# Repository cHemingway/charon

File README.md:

Remake of [carrotIndustries Pluto](https://github.com/carrotIndustries/pluto) watch (see OLD_README.md) to use Cypress PSoC4208 BLE microcontroller

Not yet manufactured, use at your own risk

PSoC4 used as it is only BLE MCU I could find with Segment LCD support.

# Credits
Major thanks to Carrot Industries for reverse engineering the display and mechanicals, this project would not be possible without this.

BME680 3D model from [3D Content Central](http://www.3dcontentcentral.com/download-model.aspx?catalogid=171&id=806790)

# Changes
- MSP430 replaced with Cypress PsOC4208 BLE MCU
- Magentometer is replaced with Bosch [BME680](https://www.bosch-sensortec.com/bst/products/all_products/bme680) Temp/Pressure/Humidity/Gas sensor
- IR reciever removed
- LED polarity fixed to save GPIO

# TODO
- Manufacture
- Bring up
- Port existing Pluto firmware

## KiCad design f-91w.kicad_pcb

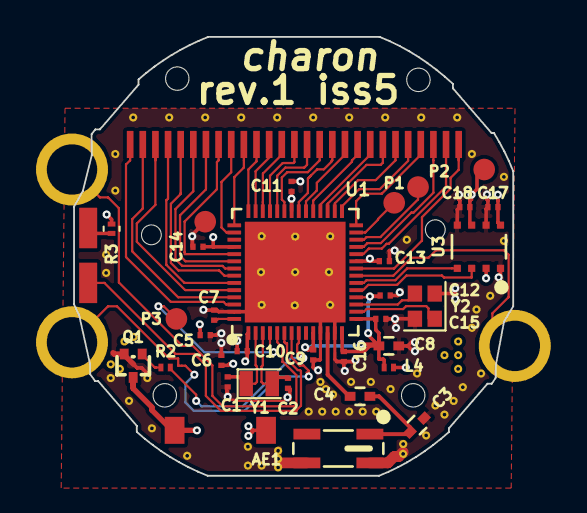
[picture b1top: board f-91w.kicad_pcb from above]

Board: 4 copper layers, 24.4 x 24.4 mm, 40 parts (0 on the bottom side), 50 nets.

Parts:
AE1: 2450AT42E0100
C1: 24pF; C_0201_NoSilk
C2: 47pF; C_0201_NoSilk
C3, C4: C_Small; C_0402
C5, C6, C7: 1uF; C_0201_NoSilk
C8: 10uF; C_0402
C9, C10, C11, C12, C13, C14, C15, C16, C17, C18: 100nF; C_0201_NoSilk
L4: 330R@100MHz; R_0201_NoSilk
P1, P2, P3: CONN_01X01; TP_1.2mm
P5, P6, P7, P8, P9, P10, P11, P13, P14: CONN_01X01; 1pin
Q1: BC847BTT1; SOT416
R2: 47k; R_0201_NoSilk
R3: 100; R_0201
U1: CY8C4248LQI-BL483; Cypress_QFN56
U2: LCD-F-91W
U3: BME680
Y1: 32.768KHz; Crystal_SMD_Abracon_ABS06-2pin_2.0x1.2mm
Y2: 24MHz; Crystal_SMD_2016-4pin_2.0x1.6mm

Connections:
//XRES: P3.1, U1.4
/BUZ: P9.1, Q1.3
/BUZ_EN: R2.1, U1.8
/B_ALARM: P7.1, U1.21
/B_LIGHT: P5.1, U1.5
/B_MODE: P6.1, U1.7
/LCD_COM1: U1.48, U2.7
/LCD_COM2: U1.47, U2.8
/LCD_COM3: U1.44, U2.9
/LCD_SEG1: U1.54, U2.1
/LCD_SEG2: U1.53, U2.2
/LCD_SEG3: U1.52, U2.3
/LCD_SEG4: U1.51, U2.4
/LCD_SEG5: U1.50, U2.5
/LCD_SEG6: U1.49, U2.6
/LCD_SEG7: U1.43, U2.10
/LCD_SEG8: U1.42, U2.11
/LCD_SEG9: U1.41, U2.12
/LCD_SEG10: U1.40, U2.13
/LCD_SEG11: U1.39, U2.14
/LCD_SEG12: U1.38, U2.15
/LCD_SEG13: U1.37, U2.16
/LCD_SEG14: U1.35, U2.17
/LCD_SEG15: U1.34, U2.18
/LCD_SEG16: U1.33, U2.19
/LCD_SEG17: U1.32, U2.20
/LCD_SEG18: U1.31, U2.21
/LCD_SEG19: U1.30, U2.22
/LCD_SEG20: U1.29, U2.23
/LCD_SEG21: U1.28, U2.24
/LCD_SEG22: U1.25, U2.25
/LCD_SEG23: U1.24, U2.26
/LCD_SEG24: U1.22, U2.27
/LED_1: P11.1, U1.6
/SCL: U1.20, U3.4
/SDA: U1.19, U3.3
/SWCLK: P1.1, U1.27
/SWDIO: P2.1, U1.26
GND: AE1.2, C1.2, C2.2, C3.2, C5.1, C6.2, C7.2, C8.2, C9.2, C10.2, C11.2, C12.2, C13.2, C14.2, C15.2, C16.2, C17.2, C18.2, P13.1, Q1.2, U1.11, U1.13, U1.55, U1.57, U3.1, U3.5, U3.7, Y2.2, Y2.4
unnamed: AE1.1, C3.1, C4.2
unnamed: C1.1, U1.2, Y1.1
unnamed: C2.1, U1.3, Y1.2
unnamed: C4.1, U1.12
unnamed: C5.2, U1.56
unnamed: P10.1, R3.1
unnamed: Q1.1, R2.2
unnamed: U1.16, Y2.1
unnamed: U1.17, Y2.3
VCC: C6.1, C7.1, C10.1, C11.1, C13.1, C14.1, C17.1, C18.1, L4.1, P8.1, P14.1, R3.2, U1.1, U1.23, U1.36, U1.46, U3.2, U3.6, U3.8
VDDR: C8.1, C9.1, C12.1, C15.1, C16.1, L4.2, U1.10, U1.14, U1.15, U1.18

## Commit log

2018-01-21 Add PSOC4200BLE QFN56 schematic symbol
2018-01-21 Remove MSP430 MCU and 32KHz Crystal
    Will replace crystal for smaller version, possibly put BLE antenna in space left.
2018-01-21 Add VDDD/VDDA/VDDR power symbols to library
2018-01-27 Add missing VDDR pin
2018-01-27 Add PSoC 4, decoupling and crystals
    No connection to rest of system yet
2018-01-27 Add missing vddr symbol library
2018-01-27 Add BME680 Temp/Humidity/Pressure/Gas sensor to library
2018-01-27 Add BME680 to schematic
2018-01-28 Add power and decoupling for PSOC
2018-01-28 Add capacitor footprints
2018-01-28 Create (unfinished) QFN56 footprint
    TODO: Customise paste mask to avoid excess solder on centre pad
2018-01-28 Add BME680 footprint
2018-01-28 PCB: First import to PCB. Lots of changes, move to 4 layer.
    Components in roughly right position, all existing traces ripped up.
    Lets us see how much space we have for BLE antenna, roughly 6.5x4x1.5mm
2018-01-28 Rewrite readme and delete old files for public release
2018-01-28 Put in design rules for PCBCart, tidy up placement
2018-01-28 Fully connect schematic
    Tested in PSoC creator, and seems routable.
2018-01-28 PCB: Route LCD display
    Some space left for debug test points, TBD
2018-01-28 More routing, add planes, crystals and decoupling caps
2018-01-28 More routing
2018-02-04 Add back in accidentally deleted mechanical holes
2018-02-04 Add Johanson 2450AT42E0100 Footprint
2018-02-04 Add Johanson 2450AT42E0100 antenna, initial placement
    TODO: Proper ground plane and 50R trace
2018-02-10 Add test points for SWD interface
2018-02-10 Reconnected traces broken by antenna placement
2018-02-10 Recede ground plane at top as per antenna requirements
2018-02-10 Add outer ground planes, keepout and stitching vias for antenna
2018-02-10 Slightly increase stiching vias around antenna
2018-02-10 Update antenna footprint to add polarity markings
2018-02-10 Remove solder paste from LCD connector, as uses zebra stripe.
    Works when hand soldering, but not if using solderpaste stencil
2018-02-10 Tidy silkscreen and gloss some tracks for demo
2018-02-10 Make antenna trace 50R coplanar to match eurocircuits stackup
2018-02-10 Fix battery connection on bottom layer and DRC errors
2018-02-10 Add ground vias in QFN centre pad
2018-02-10 REV1 ISSUE2: Fix all remaining DRC errors, check eurocircuits DFM
2018-02-11 Increase annular ring for all vias to 0.127mm
2018-02-11 Slightly tweak via spacing as per eurocircuit recommendation
2018-02-11 Remove soldermask over antenna trace
    Probably won't do much, but makes soldering network analyser easier
2018-02-11 Fix 32KHz crystal footprint for Abracon ABS06 series
2018-02-11 Add some 3D models for components
2018-02-11 Reduce solder paste coverage of QFN to ~65% for solderability
2018-02-11 Rev 1ISSUE 5: Fix final clearance
2018-02-11 RELEASE: Include all gerbers and PDF schematic, and update readme
    Now ready for production
2018-09-18 Add .gitattributes to fix showing line ending diffs
2018-09-19 Slight update to design rules for JLCPCB
2018-09-19 Change Q1 from obsolete BC846 to BC847BTT1
